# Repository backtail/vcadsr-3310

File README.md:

# vcadsr 3310
8HP Eurorack module

Voltage Contralled Envelope Generator

### Render

### Pots
Rregular ADSR behaviour

### Jacks
- **arrows**: gate input  
- **env out**: regular envelope
- **inv env**: inverse envelope

### Switches
- **speed**: `up` = fast, `down` = slow
- **offset**: `up` = inv env between -5V and 0V, `down` = inv env between 0V and 5V

## Footprints Libraries
Use provided submodule folder to link footprints locally in the project
- OS_Connectors
- OS_Scribbles

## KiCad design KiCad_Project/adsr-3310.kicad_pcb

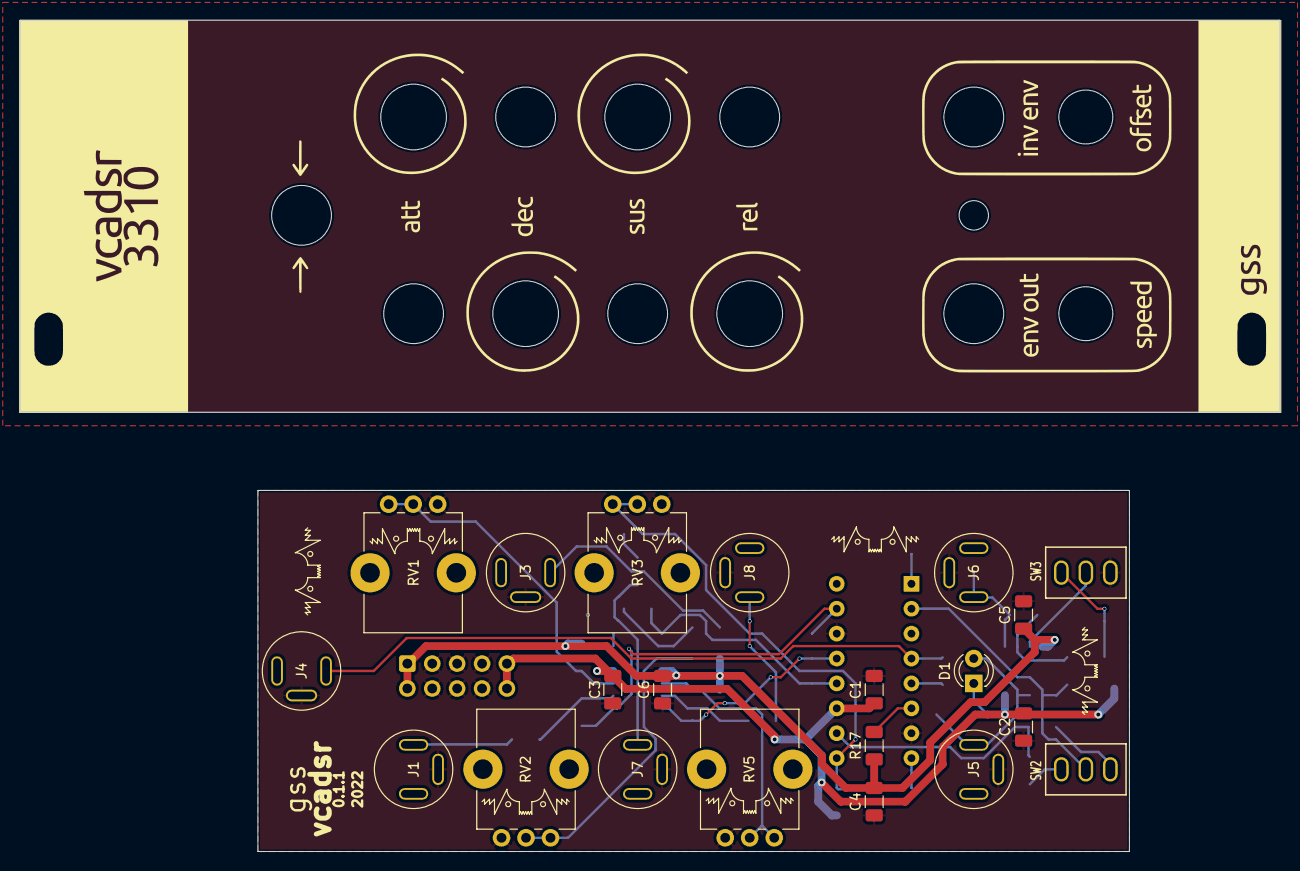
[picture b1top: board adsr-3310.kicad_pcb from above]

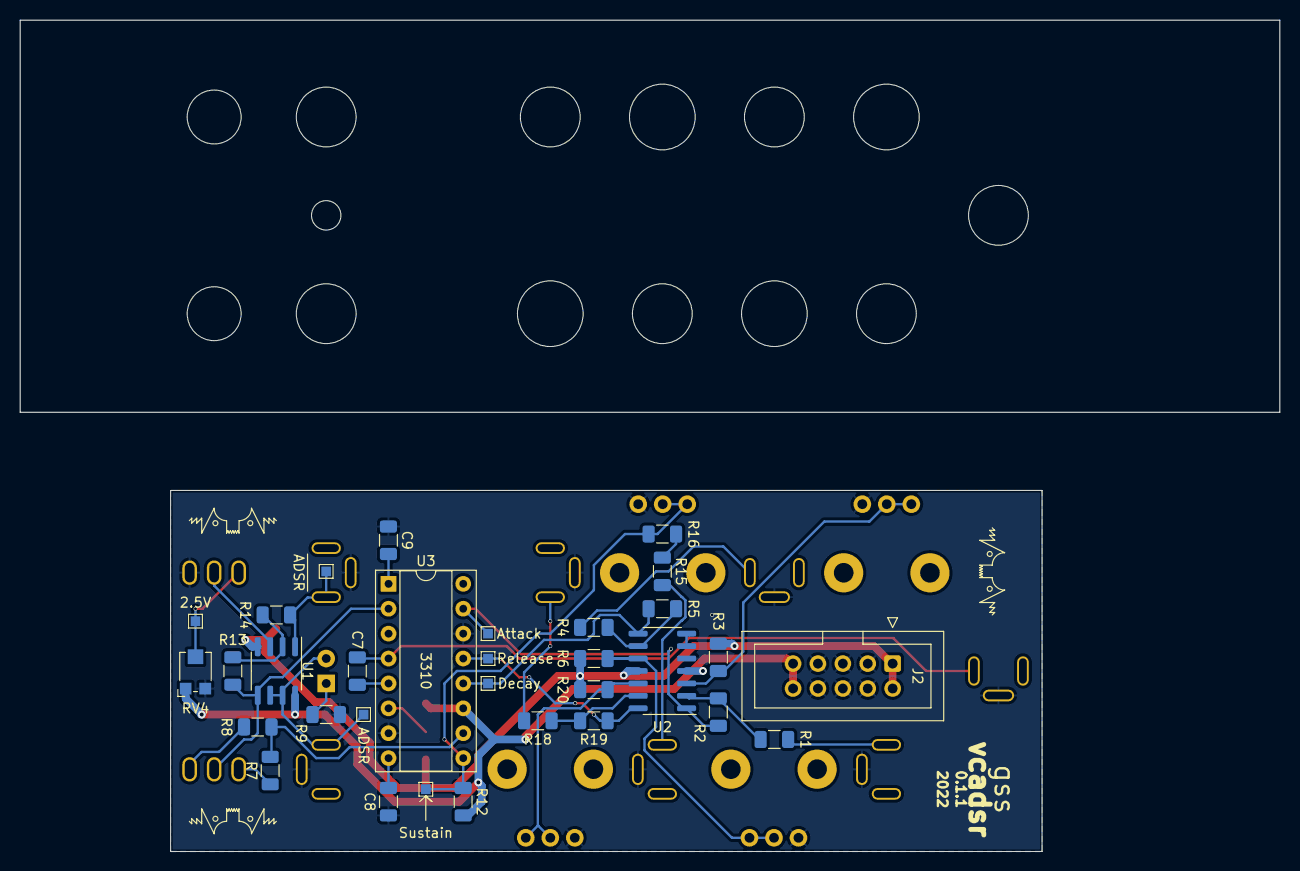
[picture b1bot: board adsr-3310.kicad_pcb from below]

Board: 2 copper layers, 88.9 x 36.8 mm, 63 parts (35 on the bottom side), 34 nets.

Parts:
2.5V: 2.5V; TestPoint_Pad_1.0x1.0mm
  : alien_small
  #2,   #3,   #4,   #5,   #6,   #7,   #8,   #9,   #10: alien_small
ADSR: ADSR; TestPoint_Pad_1.0x1.0mm
ADSR#2: inv. ADSR; TestPoint_Pad_1.0x1.0mm
Attack: [0V,-240mV]; TestPoint_Pad_1.0x1.0mm
C1, C2, C3, C4, C5, C6: 100nF; C_1206_3216Metric
C7: 3nF; C_1206_3216Metric
C8: 68nF; C_1206_3216Metric
C9: 39nF; C_1206_3216Metric
D1: Blue; LED_D3.0mm
Decay: [0V,-240mV]; TestPoint_Pad_1.0x1.0mm
J1: CV Attack; PJ-392
J2: Power; IDC-Header_2x05_P2.54mm_Vertical
J3: CV Decay; PJ-392
J4: CV Gate; PJ-392
J5: Envelope; PJ-392
J6: Inverse Env; PJ-392
J7: CV Sustain; PJ-392
J8: CV Release; PJ-392
R1, R4, R13, R14, R18: 100k; R_1206_3216Metric
R2, R5, R19: 4k7; R_1206_3216Metric
R3, R6, R20: 470k; R_1206_3216Metric
R7: 20k; R_1206_3216Metric
R8: 30k; R_1206_3216Metric
R9: 10k; R_1206_3216Metric
R12: 140k; R_1206_3216Metric
R15: 56k; R_1206_3216Metric
R16: 2k7; R_1206_3216Metric
R17: 470; R_1206_3216Metric
RV1, RV2, RV5: 10k log; Potentiometer_Alps_RK09K_Single_Vertical
RV3: 100k lin; Potentiometer_Alps_RK09K_Single_Vertical
RV4: 100k; Potentiometer_Bourns_TC33X_Vertical
Release: [0V,-240mV]; TestPoint_Pad_1.0x1.0mm
SW2, SW3: SW_SPDT; STMS-102-Micro_Toggle_Switch_SPDT
Sustain: [0V,5V]; TestPoint_Pad_1.0x1.0mm
U1: LM358; SOIC-8_3.9x4.9mm_P1.27mm
U2: TL074; SOIC-14_3.9x8.7mm_P1.27mm
U3: AS3310; DIP-16_W7.62mm_Socket

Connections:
+12V: C1.2, C2.2, C3.2, J2.9, J2.10, R12.2, RV4.1, U1.8 (V+), U2.4 (V+), U3.11 (VCC)
-12V: C4.1, C5.1, C6.1, J2.1, J2.2, R3.2, R6.2, R17.1, R20.2, U1.4 (V-), U2.11 (V-)
Attack: Attack.1, R2.1, U2.1, U3.15 (VCA)
Decay: Decay.1, R5.1, U2.8, U3.12 (VCD)
GND: C1.1, C2.1, C3.1, C4.2, C5.2, C6.2, C8.1, C9.2, J1.S, J2.3, J2.4, J2.5, J2.6, J2.7, J2.8, J3.S, J4.S, J5.S, J6.S, J7.S, J8.S, R9.1, RV1.3, RV2.3, RV3.3, RV4.3, RV5.3, SW3.3 (C), U2.5 (+), U3.7 (PGND), U3.14 (GND)
unnamed: C7.1, U3.5 (TRIG)
unnamed: C7.2, J4.T, U3.4 (GATE)
unnamed: C8.2, U3.8 (CCOMP)
unnamed: C9.1, U3.1 (CAP)
unnamed: D1.1 (K), R9.2
unnamed: ADSR.1, D1.2 (A), J5.T, U1.6 (-), U1.7
unnamed: J1.T, R1.2
unnamed: J3.T, R4.2
unnamed: ADSR#2.1, J6.T, R14.1, U1.1
unnamed: J7.T, R15.2
unnamed: J8.T, R18.2
unnamed: R1.1, R2.2, U2.2 (-)
unnamed: R3.1, RV1.1, RV1.2, U2.3 (+)
unnamed: R4.1, R5.2, U2.9 (-)
unnamed: R6.1, RV2.1, RV2.2, U2.10 (+)
unnamed: R7.1, SW2.1 (A)
unnamed: R7.2, R8.1, U3.10 (IIN)
unnamed: R8.2, SW2.3 (C)
unnamed: R13.1, R14.2, U1.2 (-)
unnamed: R13.2, SW2.2 (B), U1.5 (+), U3.2 (ENVOUT)
unnamed: R15.1, R16.2
unnamed: R17.2, U3.6 (VEE)
unnamed: R18.1, R19.2, U2.13 (-)
unnamed: R20.1, RV5.1, RV5.2, U2.12 (+)
unnamed: 2.5V.1, RV4.2, SW3.1 (A)
unnamed: SW3.2 (B), U1.3 (+)
unnamed: U2.6 (-), U2.7
Release: R19.1, Release.1, U2.14, U3.13 (VCR)
Sustain: R12.1, R16.1, RV3.1, RV3.2, Sustain.1, U3.9 (VCS)

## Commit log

2022-03-15 inital commit
2022-03-15 add footprints submodule
2022-03-15 add BOM
2022-03-15 wind of change
2024-10-23 add fp png
